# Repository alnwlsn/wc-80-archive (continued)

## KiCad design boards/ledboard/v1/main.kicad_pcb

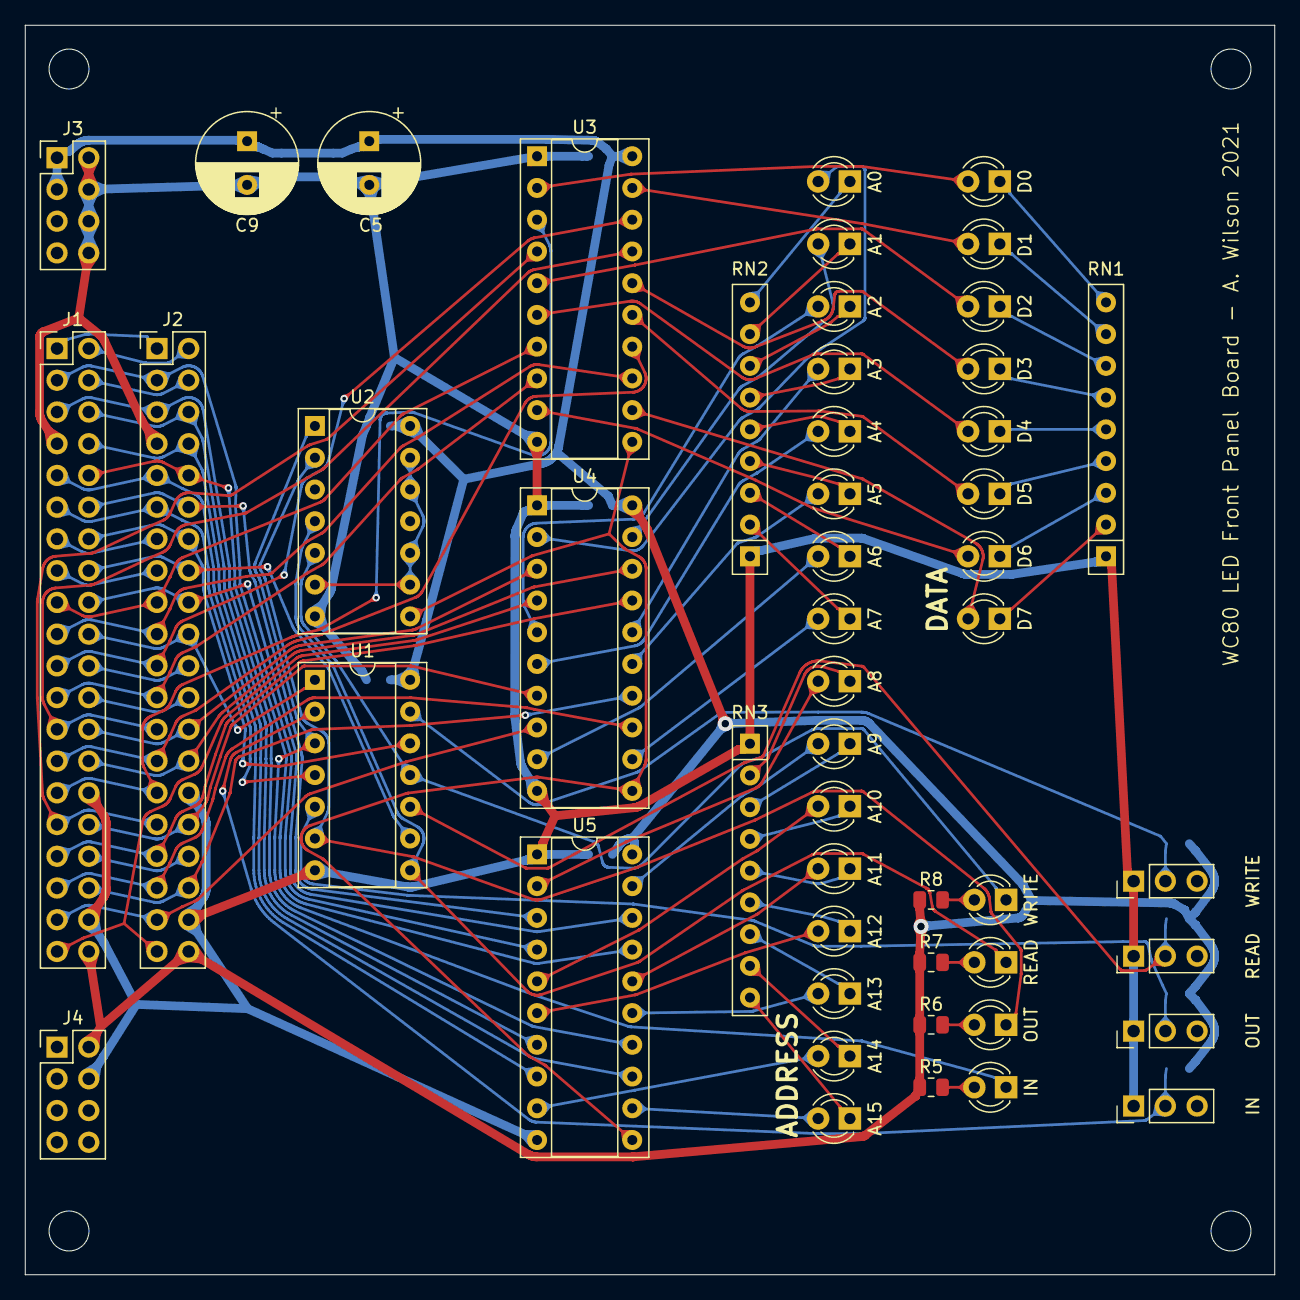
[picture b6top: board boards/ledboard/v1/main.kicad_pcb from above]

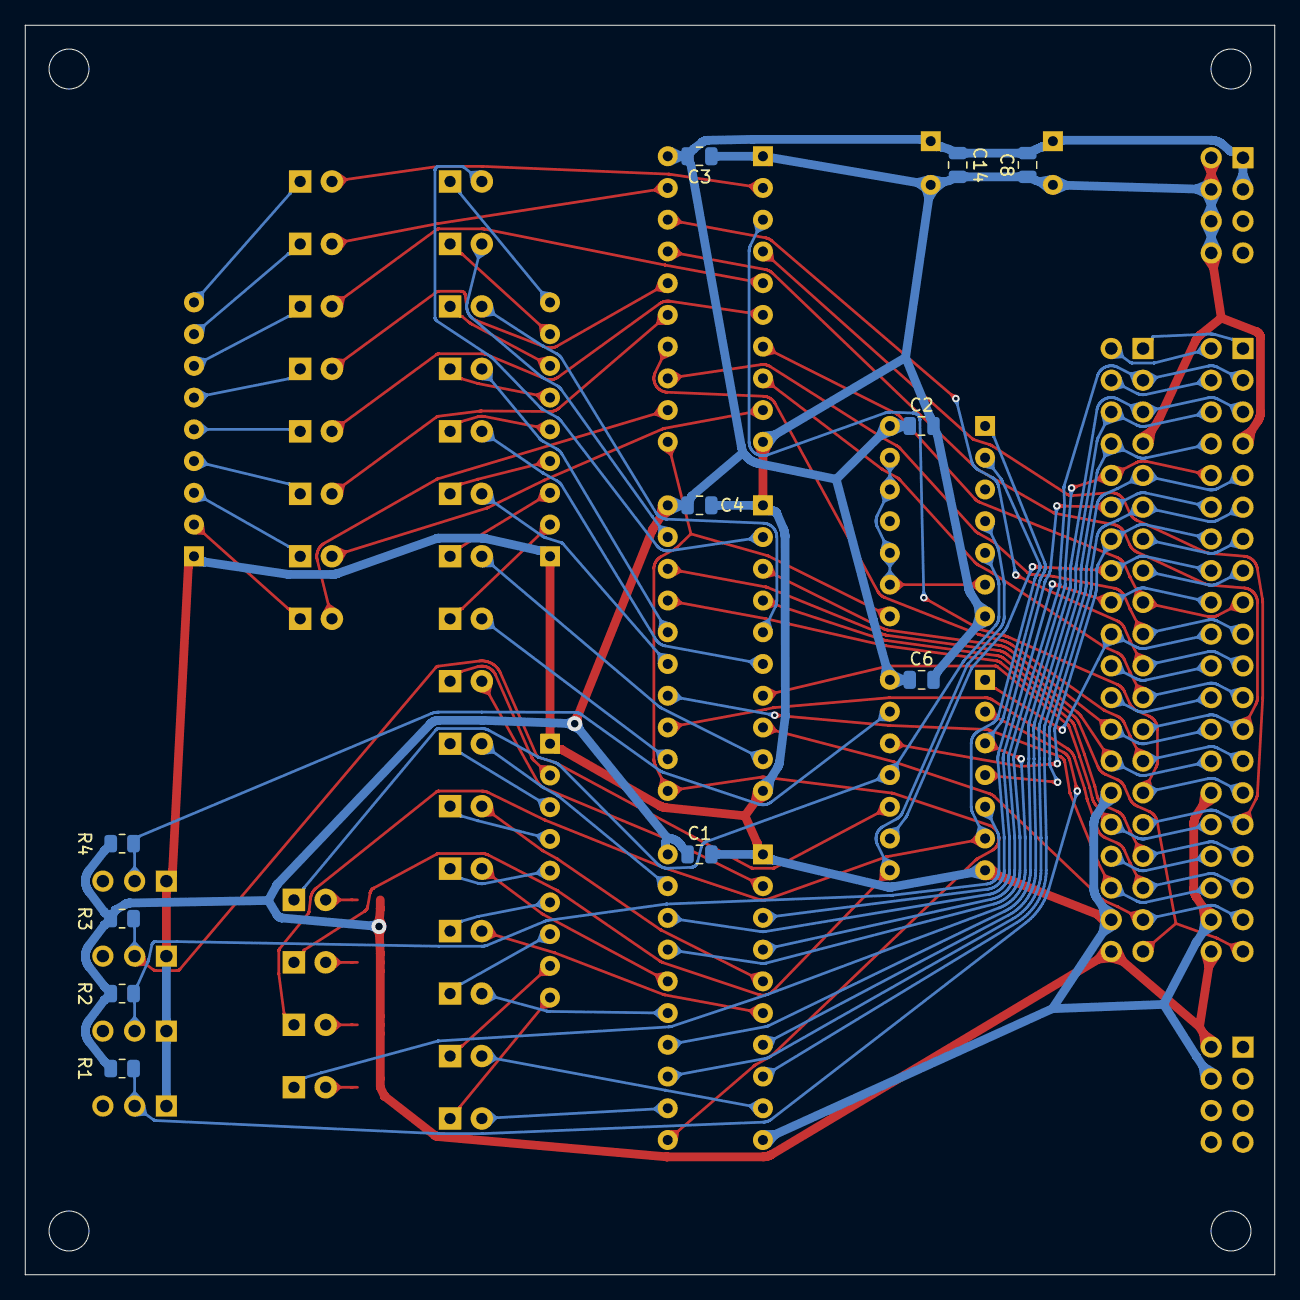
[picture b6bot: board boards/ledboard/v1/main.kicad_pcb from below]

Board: 2 copper layers, 100.0 x 100.0 mm, 65 parts (11 on the bottom side), 100 nets.

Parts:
C1, C2, C3, C4, C6, C8, C14: 100n; C_0805_2012Metric
C5, C9: 470uF; CP_Radial_D8.0mm_P3.50mm
D1: D0; LED_D3.0mm_FlatTop
D2: D2; LED_D3.0mm_FlatTop
D3: D4; LED_D3.0mm_FlatTop
D4: D6; LED_D3.0mm_FlatTop
D5: D7; LED_D3.0mm_FlatTop
D6: D5; LED_D3.0mm_FlatTop
D7: D3; LED_D3.0mm_FlatTop
D8: D1; LED_D3.0mm_FlatTop
D9: A0; LED_D3.0mm_FlatTop
D10: A2; LED_D3.0mm_FlatTop
D11: A4; LED_D3.0mm_FlatTop
D12: A6; LED_D3.0mm_FlatTop
D13: A7; LED_D3.0mm_FlatTop
D14: A5; LED_D3.0mm_FlatTop
D15: A3; LED_D3.0mm_FlatTop
D16: A1; LED_D3.0mm_FlatTop
D17: A8; LED_D3.0mm_FlatTop
D18: A10; LED_D3.0mm_FlatTop
D19: A12; LED_D3.0mm_FlatTop
D20: A14; LED_D3.0mm_FlatTop
D21: A15; LED_D3.0mm_FlatTop
D22: A13; LED_D3.0mm_FlatTop
D23: A11; LED_D3.0mm_FlatTop
D24: A9; LED_D3.0mm_FlatTop
D25: IN; LED_D3.0mm_FlatTop
D26: OUT; LED_D3.0mm_FlatTop
D27: READ; LED_D3.0mm_FlatTop
D28: WRITE; LED_D3.0mm_FlatTop
H1, H2, H3, H4: MountingHole; MountingHole_3.2mm_M3_DIN965
J1, J2: TRS80W-header; PinHeader_2x20_P2.54mm_Vertical
J3, J4: Conn_02x04_Odd_Even; PinHeader_2x04_P2.54mm_Vertical
R1, R2, R3, R4: 4.7K; R_0805_2012Metric
R5, R6, R7, R8: 470; R_0805_2012Metric
RN1, RN2, RN3: 470; R_Array_SIP9
SW1: IN; PinHeader_1x03_P2.54mm_Vertical
SW2: OUT; PinHeader_1x03_P2.54mm_Vertical
SW3: READ; PinHeader_1x03_P2.54mm_Vertical
SW4: WRITE; PinHeader_1x03_P2.54mm_Vertical
U1: 74LS32; DIP-14_W7.62mm_Socket
U2: 74LS20; DIP-14_W7.62mm_Socket
U3, U4, U5: 74LS374; DIP-20_W7.62mm_Socket

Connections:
+5V: C1.1, C2.1, C3.1, C4.1, C5.1, C6.1, C8.1, C9.1, C14.1, J1.40, J2.40, J3.1, J3.3, J4.2, R1.1, R2.1, R3.1, R4.1, R5.1, R6.1, R7.1, R8.1, U1.14, U2.14, U3.20, U4.20, U5.20
CLK: J1.24, J2.24
F_A0: J1.26, J2.26, U4.3
F_A1: J1.28, J2.28, U4.18
F_A2: J1.39, J2.39, U4.4
F_A3: J1.33, J2.33, U4.17
F_A4: J1.32, J2.32, U4.7
F_A5: J1.36, J2.36, U4.14
F_A6: J1.37, J2.37, U4.8
F_A7: J1.35, J2.35, U4.13
F_A8: J1.12, J2.12, U5.3
F_A9: J1.18, J2.18, U5.18
F_A10: J1.3, J2.3, U5.4
F_A11: J1.10, J2.10, U5.17
F_A12: J1.6, J2.6, U5.7
F_A13: J1.5, J2.5, U5.14
F_A14: J1.9, J2.9, U5.8
F_A15: J1.8, J2.8, U5.13
F_D0: J1.29, J2.29, U3.3
F_D1: J1.21, J2.21, U3.18
F_D2: J1.31, J2.31, U3.4
F_D3: J1.25, J2.25, U3.17
F_D4: J1.17, J2.17, U3.7
F_D5: J1.27, J2.27, U3.14
F_D6: J1.23, J2.23, U3.8
F_D7: J1.19, J2.19, U3.13
GND: C1.2, C2.2, C3.2, C4.2, C5.2, C6.2, C8.2, C9.2, C14.2, J1.7, J1.30, J1.38, J2.7, J2.30, J2.38, J3.2, J3.4, J3.6, J3.8, J4.4, RN1.1, RN2.1, RN3.1, SW1.1, SW2.1, SW3.1, SW4.1, U1.7, U2.7, U3.1, U3.10, U4.1, U4.10, U5.1, U5.10
unnamed: D1.1, RN1.9
unnamed: D1.2, U3.2
unnamed: D2.1, RN1.7
unnamed: D2.2, U3.5
unnamed: D3.1, RN1.5
unnamed: D3.2, U3.6
unnamed: D4.1, RN1.3
unnamed: D4.2, U3.9
unnamed: D5.1, RN1.2
unnamed: D5.2, U3.12
unnamed: D6.1, RN1.4
unnamed: D6.2, U3.15
unnamed: D7.1, RN1.6
unnamed: D7.2, U3.16
unnamed: D8.1, RN1.8
unnamed: D8.2, U3.19
unnamed: D9.1, RN2.9
unnamed: D9.2, U4.2
unnamed: D10.1, RN2.7
unnamed: D10.2, U4.5
unnamed: D11.1, RN2.5
unnamed: D11.2, U4.6
unnamed: D12.1, RN2.3
unnamed: D12.2, U4.9
unnamed: D13.1, RN2.2
unnamed: D13.2, U4.12
unnamed: D14.1, RN2.4
unnamed: D14.2, U4.15
unnamed: D15.1, RN2.6
unnamed: D15.2, U4.16
unnamed: D16.1, RN2.8
unnamed: D16.2, U4.19
unnamed: D17.1, RN3.2
unnamed: D17.2, U5.2
unnamed: D18.1, RN3.4
unnamed: D18.2, U5.5
unnamed: D19.1, RN3.6
unnamed: D19.2, U5.6
unnamed: D20.1, RN3.8
unnamed: D20.2, U5.9
unnamed: D21.1, RN3.9
unnamed: D21.2, U5.12
unnamed: D22.1, RN3.7
unnamed: D22.2, U5.15
unnamed: D23.1, RN3.5
unnamed: D23.2, U5.16
unnamed: D24.1, RN3.3
unnamed: D24.2, U5.19
unnamed: D25.1, U1.3, U2.1
unnamed: D25.2, R5.2
unnamed: D26.1, U1.6, U2.2
unnamed: D26.2, R6.2
unnamed: D27.1, U1.8, U2.4
unnamed: D27.2, R7.2
unnamed: D28.1, U1.11, U2.5
unnamed: D28.2, R8.2
unnamed: R1.2, SW1.2, U1.2
unnamed: R2.2, SW2.2, U1.5
unnamed: R3.2, SW3.2, U1.10
unnamed: R4.2, SW4.2, U1.13
unnamed: U2.8, U3.11, U4.11, U5.11
unnamed: U2.6, U2.9, U2.10, U2.12, U2.13
~F_EXMEM~: J1.4, J2.4
~F_INTAK~: J1.13, J2.13
~F_INT~: J1.22, J2.22
~F_INUSE~: J1.15, J2.15
~F_IN~: J1.20, J2.20, U1.1
~F_MREQ~: J1.2, J2.2
~F_OUT~: J1.11, J2.11, U1.4
~F_READ~: J1.16, J2.16, U1.9
~F_SYSRES~: J1.1, J2.1
~F_WAIT~: J1.34, J2.34
~F_WRITE~: J1.14, J2.14, U1.12

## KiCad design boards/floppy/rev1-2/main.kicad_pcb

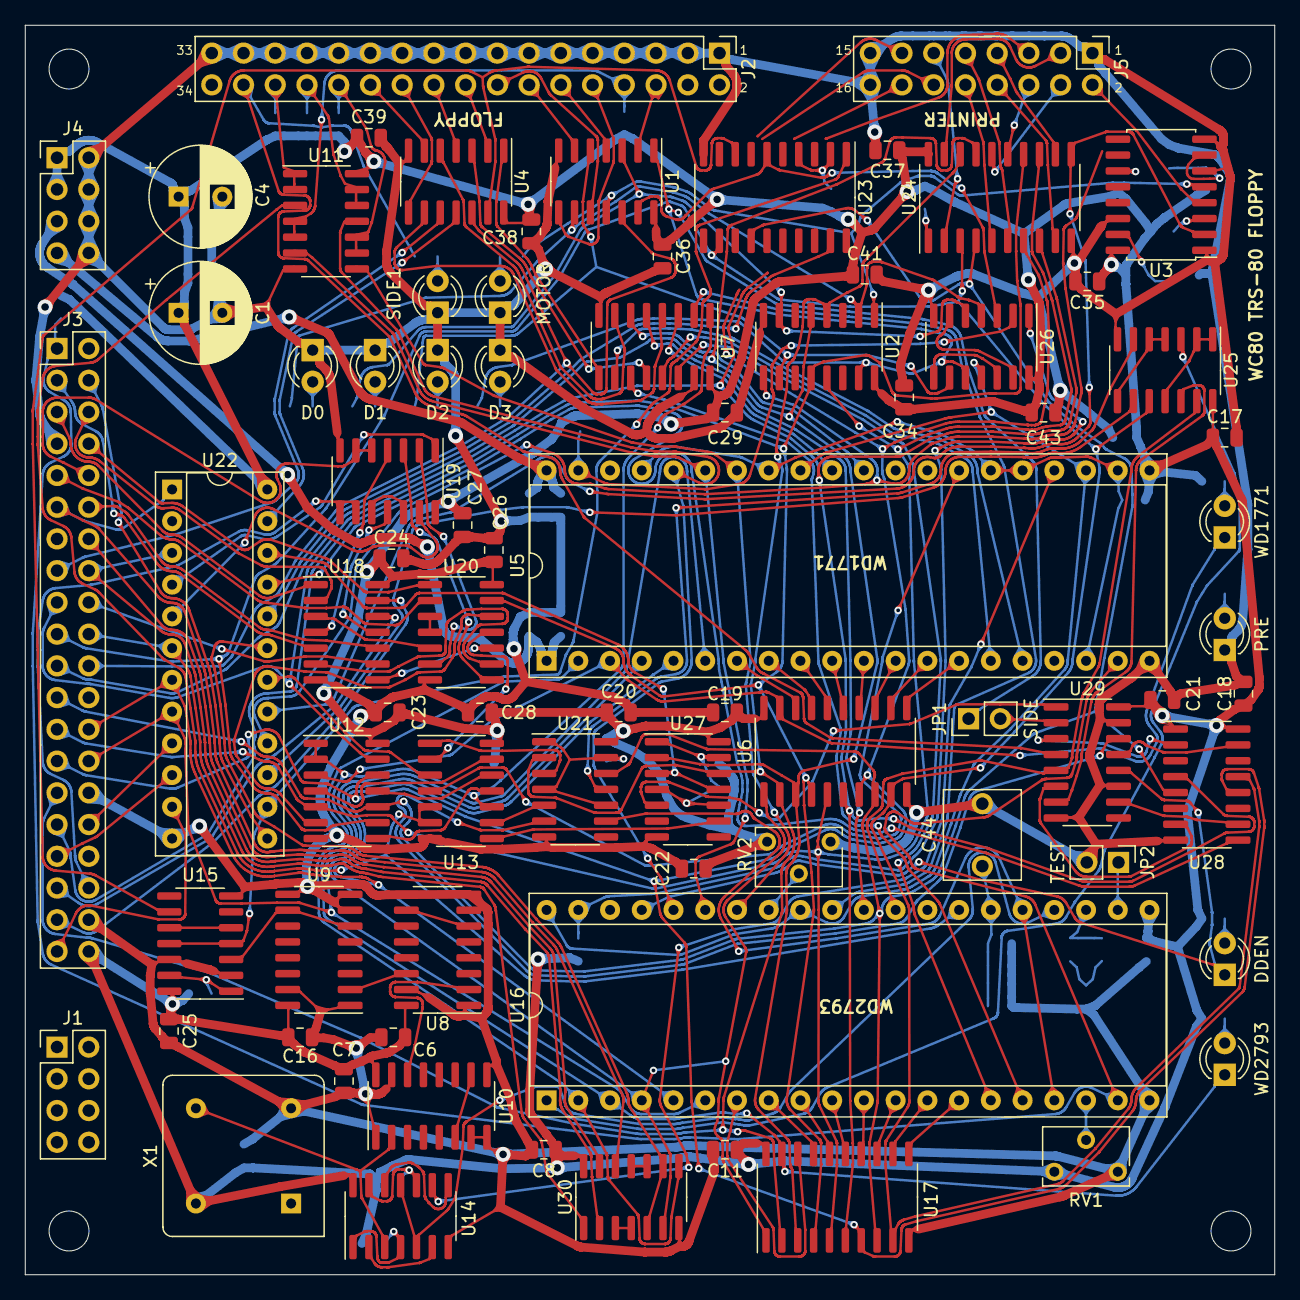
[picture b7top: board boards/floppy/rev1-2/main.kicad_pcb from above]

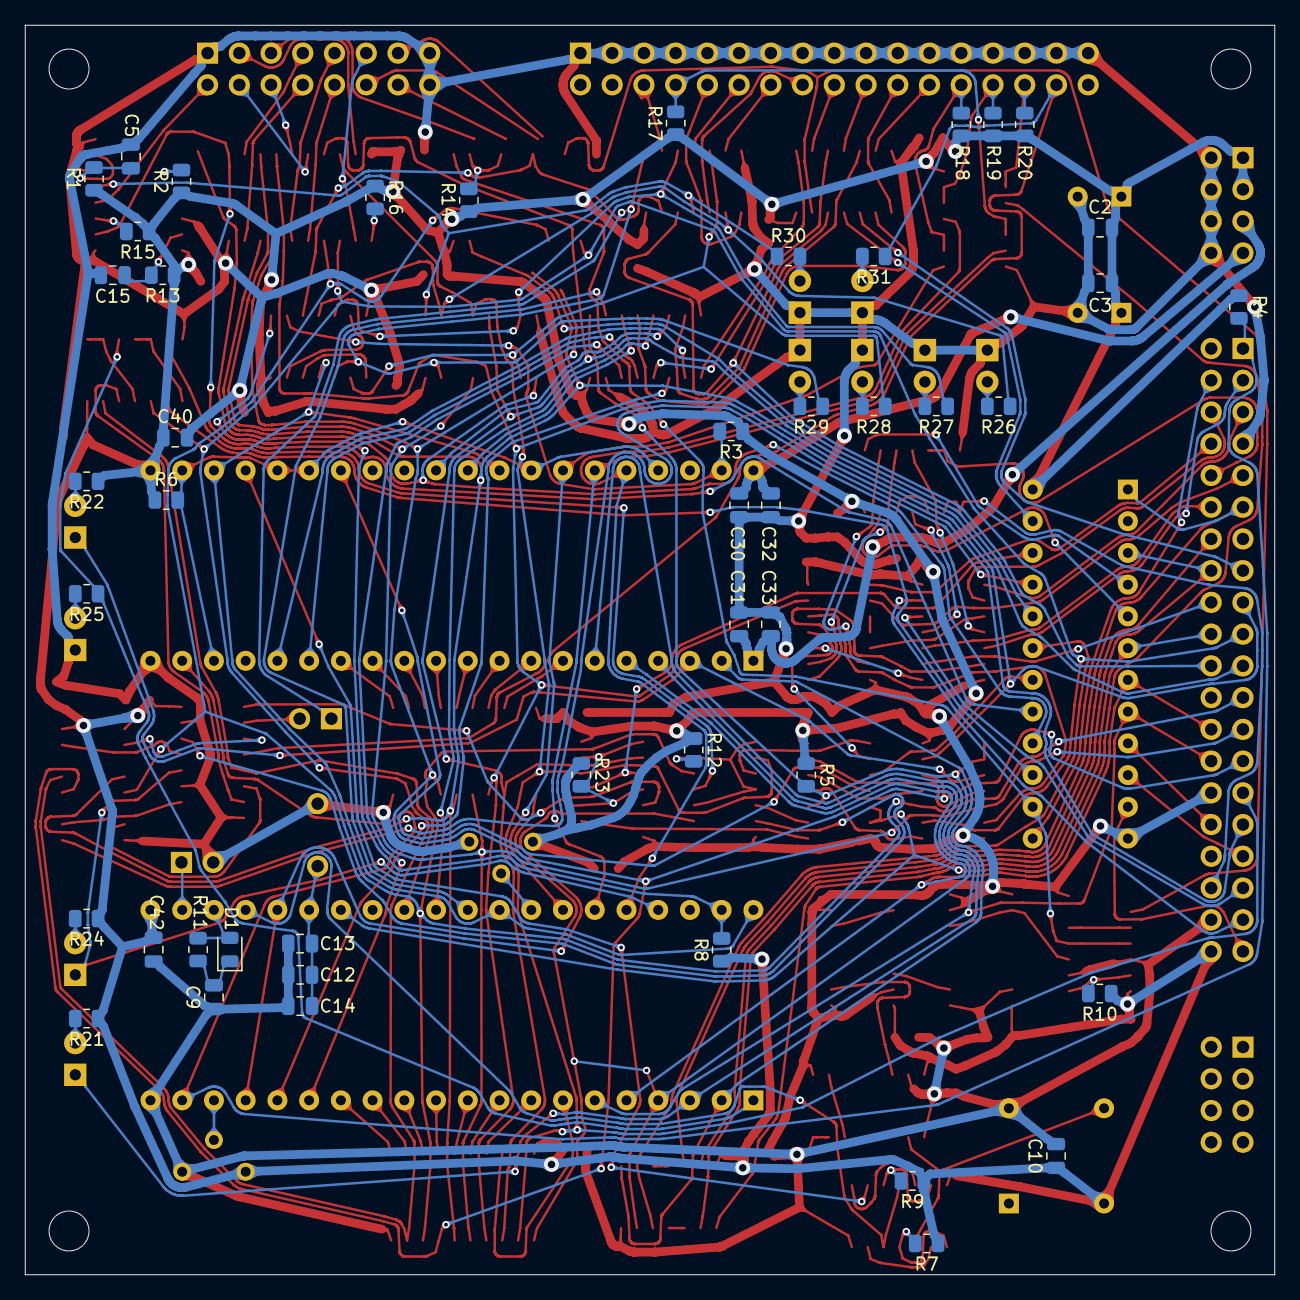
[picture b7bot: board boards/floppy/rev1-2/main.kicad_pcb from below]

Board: 2 copper layers, 100.0 x 100.0 mm, 130 parts (47 on the bottom side), 198 nets.

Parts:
C1, C4: 470uF; CP_Radial_D8.0mm_P3.50mm
C2, C3, C6, C7, C8, C10, C11, C16, C17, C18, C19, C20, C21, C22, C23, C24, C25, C26, C27, C28, C29, C30, C31, C32, C33, C34, C35, C36, C37, C38, C39, C40, C41, C42, C43: 100n; C_0805_2012Metric
C5: 33uF; C_0805_2012Metric
C9: 150nF; C_0805_2012Metric
C12, C13, C14: 15pF; C_0805_2012Metric
C15: 200p; C_0805_2012Metric
C44: 60pF; C_Rect_L7.0mm_W6.0mm_P5.00mm
D1: DIODE; D_0805_2012Metric
D2: WD2793; LED_D3.0mm
D3: WD1771; LED_D3.0mm
D4: DDEN; LED_D3.0mm
D5: PRE; LED_D3.0mm
D6: D0; LED_D3.0mm
D7: D1; LED_D3.0mm
D8: D2; LED_D3.0mm
D9: D3; LED_D3.0mm
D10: MOTOR; LED_D3.0mm
D11: SIDE1; LED_D3.0mm
J1, J4: Conn_02x04_Odd_Even; PinHeader_2x04_P2.54mm_Vertical
J2: Floppy-header; PinHeader_2x17_P2.54mm_Vertical
J3: TRS80W-header; PinHeader_2x20_P2.54mm_Vertical
J5: Conn_01x16_Male; PinHeader_2x08_P2.54mm_Vertical
JP1: SIDE; PinHeader_1x02_P2.54mm_Vertical
JP2: TEST; PinHeader_1x02_P2.54mm_Vertical
M1, M2, M3, M4: 3mm-mounting-hole; MountingHole_3.2mm_M3_DIN965
R1: 200K; R_0805_2012Metric
R2, R15, R16: 4K7; R_0805_2012Metric
R3, R4, R5, R6, R7, R8, R9, R10, R12, R14, R23: 10K; R_0805_2012Metric
R11: 1K; R_0805_2012Metric
R13: 20K; R_0805_2012Metric
R17, R18, R19, R20: 150; R_0805_2012Metric
R21, R22, R24, R25, R26, R27, R28, R29, R30, R31: 470; R_0805_2012Metric
RV1: 50K; Potentiometer_Bourns_3266W_Vertical
RV2: 10K; Potentiometer_Bourns_3266W_Vertical
U1, U4: 74LS06; SOIC-14_3.9x8.7mm_P1.27mm
U2, U28: 74LS175; SOP-16_3.9x9.9mm_P1.27mm
U3: 74LS123; SO-16_5.3x10.2mm_P1.27mm
U5: WD1771; DIP-40_W15.24mm_Socket
U6: 74LS640; SO-20_5.3x12.6mm_P1.27mm
U7, U29: 74LS157; SOP-16_3.9x9.9mm_P1.27mm
U8, U9, U10: 4518; SOP-16_3.9x9.9mm_P1.27mm
U11: 74LS08; SOIC-14_3.9x8.7mm_P1.27mm
U12, U18, U25, U30: 74LS00; SOIC-14_3.9x8.7mm_P1.27mm
U13, U19: 74LS02; SOIC-14_3.9x8.7mm_P1.27mm
U14, U15, U21, U27: 74LS74; SOIC-14_3.9x8.7mm_P1.27mm
U16: WD2793; DIP-40_W15.24mm_Socket
U17: 74LS245; SO-20_5.3x12.6mm_P1.27mm
U20, U26: 74LS32; SOIC-14_3.9x8.7mm_P1.27mm
U22: ATF22V10C; DIP-24_W7.62mm_Socket
U23: 74LS244; SO-20_5.3x12.6mm_P1.27mm
U24: 74LS273; SO-20_5.3x12.6mm_P1.27mm
X1: CXO_DIP8; Oscillator_DIP-8

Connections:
1MHz: U5.24, U14.9
2MHz: U14.5, U14.11, U16.24
4MHz: U10.2, U14.3, X1.5
37XX: U19.1, U22.4
40Hz: U9.6, U9.10, U15.3
58SEL: U22.15, U25.9
+5V: C1.1, C2.1, C3.1, C4.1, C6.1, C7.1, C8.1, C10.1, C11.1, C16.1, C17.1, C18.1, C19.1, C20.1, C21.1, C22.1, C23.1, C24.1, C25.1, C26.1, C27.1, C28.1, C29.1, C34.1, C35.1, C36.1, C37.1, C38.1, C39.1, C40.1, C41.1, C42.1, C43.1, J3.40, J4.1, J4.3, R1.1, R2.1, R3.1, R4.1, R5.1, R6.1, R7.1, R8.1, R9.1, R10.1, R12.1, R13.1, R14.1, R15.1, R16.1, R17.1, R18.1, R19.1, R20.1, R21.1, R22.1, R23.1, R24.1, RV1.1, RV2.3, U1.14, U2.16, U3.16, U4.14, U5.21, U6.20, U7.16, U8.16, U9.16, U10.16, U11.14, U12.14, U13.14, U14.14, U15.14, U16.21, U17.20, U18.14, U19.14, U20.14, U21.14, U22.24, U23.20, U24.20, U25.14, U26.14, U27.14, U28.1, U29.16, U30.14, X1.8
+12V: C30.1, C32.1, J4.7, U5.40
-5V: C31.1, C33.1, J4.5, U5.1
CENP: R25.1, U16.1, U25.3
D0: R26.1, U1.9, U2.2, U26.4
D1: R27.1, U1.3, U2.7, U26.5
D2: R28.1, U1.5, U2.10, U26.9
D3: JP1.1, R29.1, U1.1, U2.15, U26.10
DFH: U22.21, U28.9
DFL: U2.9, U3.9, U22.16
EFX: U19.13, U22.5
FLOP: U22.19, U30.5, U30.9
FSIDE: J2.32, R31.1, U29.4
F_A0: J3.26, U5.5, U16.5, U22.7
F_A1: J3.28, U5.6, U16.6, U22.8
F_A2: J3.39, U22.11
F_A3: J3.33, U22.10
F_A4: J3.32, U22.9
F_A5: J3.36, U19.8, U19.9
F_A6: J3.37, U18.13
F_A7: J3.35, U18.12
F_A8: J3.12, U18.10
F_A9: J3.18, U18.9
F_A10: J3.3, U18.5
F_A11: J3.10, U19.5, U19.6
F_A12: J3.6, U18.2
F_A13: J3.5, U18.1
F_A14: J3.9, U20.2
F_A15: J3.8, U20.1
F_D0: J3.29, U2.4, U6.2, U17.2, U21.2, U24.18, U27.12
F_D1: J3.21, U2.5, U6.3, U17.3, U24.17, U27.2
F_D2: J3.31, U2.12, U6.4, U17.4, U20.13, U24.14
F_D3: J3.25, U2.13, U6.5, U12.5, U17.5, U24.13
F_D4: J3.17, U6.6, U12.13, U17.6, U23.3, U24.8, U28.4
F_D5: J3.27, U6.7, U12.12, U17.7, U23.5, U24.7, U28.12
F_D6: J3.23, U6.8, U12.10, U17.8, U21.12, U23.7, U23.14, U24.4, U28.5
F_D7: J3.19, U6.9, U12.9, U17.9, U23.9, U23.12, U24.3, U25.10, U28.13
GND: C1.2, C2.2, C3.2, C4.2, C5.2, C6.2, C7.2, C8.2, C9.1, C10.2, C11.2, C12.1, C13.1, C14.1, C15.2, C16.2, C17.2, C18.2, C19.2, C20.2, C21.2, C22.2, C23.2, C24.2, C25.2, C26.2, C27.2, C28.2, C29.2, C30.2, C31.2, C32.2, C33.2, C34.2, C35.2, C36.2, C37.2, C38.2, C39.2, C40.2, C41.2, C42.2, C43.2, C44.2, D5.1, D6.1, D7.1, D8.1, D9.1, D10.1, D11.1, J2.1, J2.3, J2.5, J2.7, J2.9, J2.11, J2.13, J2.15, J2.17, J2.19, J2.21, J2.23, J2.25, J2.27, J2.29, J2.31, J2.33, J3.7, J3.30, J3.38, J4.2, J4.4, J4.6, J4.8, J5.1, J5.15, J5.16, JP2.2, RV1.3, RV2.1, U1.7, U2.8, U3.1, U3.6, U3.8, U3.14, U4.7, U5.20, U6.10, U7.8, U7.15, U8.1, U8.7, U8.8, U8.9, U8.15, U9.1, U9.7, U9.8, U9.9, U9.15, U10.1, U10.7, U10.8, U10.9, U10.15, U11.7, U12.7, U13.7, U14.7, U15.2, U15.7, U15.12, U16.20, U17.10, U18.7, U19.7, U20.7, U21.7, U22.12, U23.10, U24.10, U25.7, U26.7, U27.7, U28.8, U29.8, U29.11, U29.15, U30.7, X1.4
INTCLK: U4.13, U15.9, U23.8
INTFLOP: U1.13, U23.6
M1PRE: U16.29, U25.13, U29.5
M1SIDE: JP1.2, U29.2
MOTOR: R30.1, U1.11, U2.1, U3.5
unnamed: C5.1, R1.2, U3.7
unnamed: C9.2, D1.1, R11.1
unnamed: C12.2, C13.2, C14.2, C44.1, U16.26
unnamed: C15.1, R13.2, U3.15
unnamed: D1.2, R11.2, U16.23
unnamed: D2.2, R21.2
unnamed: D3.2, R22.2
unnamed: D4.2, R24.2
unnamed: D5.2, R25.2
unnamed: D6.2, R26.2
unnamed: D7.2, R27.2
unnamed: D8.2, R28.2
unnamed: D9.2, R29.2
unnamed: D10.2, R30.2
unnamed: D11.2, R31.2
unnamed: J2.6, U1.2
unnamed: J2.8, R17.2
unnamed: J2.10, U1.8
unnamed: J2.12, U1.4
unnamed: J2.14, U1.6
unnamed: J2.16, U1.10
unnamed: J2.18, U4.2
unnamed: J2.20, U4.4
unnamed: J2.22, U4.8
unnamed: J2.24, U4.6
unnamed: J2.26, R18.2
unnamed: J2.28, R19.2
unnamed: J2.30, R20.2, U26.1, U26.2
unnamed: J5.2, U3.4
unnamed: J5.3, U24.19
unnamed: J5.4, U24.16
unnamed: J5.5, U23.17
unnamed: J5.6, U24.15
unnamed: J5.7, U24.12
unnamed: J5.8, U24.9
unnamed: J5.9, U24.6
unnamed: J5.10, U24.5
unnamed: J5.11, U24.2
unnamed: J5.12, U23.11
unnamed: J5.13, U23.13
unnamed: J5.14, U23.15
unnamed: JP2.1, U16.22
unnamed: R2.2, U3.10, U3.11
unnamed: R3.2, U5.39
unnamed: R6.2, U5.18, U5.22, U5.25, U5.26, U5.33, U5.37
unnamed: R7.2, U14.1, U14.4
unnamed: R8.2, U16.39
unnamed: R9.2, U14.10, U14.13
unnamed: R10.2, U15.1, U15.13
unnamed: R12.2, U21.1, U21.4, U21.10, U21.13
unnamed: R14.2, U23.2, U23.4
unnamed: R15.2, U3.3
unnamed: R16.2, U24.1
unnamed: R23.2, U27.1, U27.4, U27.10, U27.13
unnamed: RV1.2, U16.18
unnamed: RV2.2, U16.33
unnamed: U4.1, U7.9
unnamed: U4.3, U7.12
unnamed: U4.5, U7.7
unnamed: U4.9, U7.4
unnamed: U5.7, U6.18
unnamed: U5.8, U6.17
unnamed: U5.9, U6.16
unnamed: U5.10, U6.15
unnamed: U5.11, U6.14
unnamed: U5.12, U6.13
unnamed: U5.13, U6.12
unnamed: U5.14, U6.11
unnamed: U5.15, U7.13
unnamed: U5.16, U7.10
unnamed: U5.30, U7.6
unnamed: U5.31, U7.3
unnamed: U8.6, U8.10
unnamed: U8.14, U9.2
unnamed: U10.6, U10.10
unnamed: U8.2, U10.14
unnamed: U12.4, U13.13
unnamed: U12.6, U20.12
unnamed: U12.8, U13.11
unnamed: U12.11, U13.12
unnamed: U13.1, U21.3
unnamed: U13.2, U20.11
unnamed: U5.27, U13.4
unnamed: U13.5, U13.6, U16.27, U26.3
unnamed: U13.8, U27.9
unnamed: U13.9, U21.5
unnamed: U14.2, U14.6
unnamed: U14.8, U14.12
unnamed: U15.5, U15.10
unnamed: U5.2, U16.2, U30.8
unnamed: U5.4, U6.1, U16.4, U17.1, U30.6
unnamed: U16.7, U17.18
unnamed: U16.8, U17.17
unnamed: U16.9, U17.16
unnamed: U16.10, U17.15
unnamed: U16.11, U17.14
unnamed: U16.12, U17.13
unnamed: U16.13, U17.12
unnamed: U16.14, U17.11
unnamed: U7.14, U16.15
unnamed: U7.11, U16.16
unnamed: U16.17, U16.25, U21.9
unnamed: U7.5, U16.30
unnamed: U7.2, U16.31
unnamed: U5.23, U5.32, U16.32, U16.40, U26.11
unnamed: U5.34, U16.34
unnamed: U5.35, U16.35
unnamed: U5.36, U16.36
unnamed: U18.3, U20.5
unnamed: U18.4, U19.4
unnamed: U18.6, U20.9
unnamed: U18.8, U20.10
unnamed: U18.11, U19.11
unnamed: U19.2, U20.6
unnamed: U19.3, U20.8
unnamed: U19.10, U19.12
unnamed: U20.3, U20.4
unnamed: U21.11, U25.6
unnamed: U4.11, U22.23
unnamed: U25.1, U25.2, U25.11
unnamed: U25.4, U25.5, U25.8
unnamed: U25.12, U29.7
unnamed: U26.8, U26.12
unnamed: U26.6, U26.13
unnamed: U27.5, U29.1
unnamed: U28.2, U29.3
unnamed: U28.7, U29.6
unnamed: U28.10, U29.10
unnamed: U28.15, U29.13
unnamed: U30.3, U30.4
unnamed: U30.10, U30.11
OPT: U22.22, U27.3, U27.11
~37E0~: U15.4, U15.11, U22.14, U23.1
~1771~: D3.1, U5.3, U6.19, U12.3
~2793~: D2.1, R5.2, U7.1, U12.1, U12.2, U13.10, U16.3, U17.19
~CDDEN~: D4.1, U16.37, U29.12
~DENSEL~: U13.3, U22.18
~F_EXMEM~: J3.4, U22.13
~F_INT~: J3.22, U1.12, U4.12
~F_INUSE~: J3.15, U4.10
~F_IN~: J3.20, U22.6, U30.1
~F_MEMRQ~: J3.2, U22.2
~F_OUT~: J3.11, U22.1, U30.12
~F_READ~: J3.16, U22.3, U30.2
~F_SYSRES~: J3.1, R4.2, U5.19, U16.19
~F_WRITE~: J3.14, U30.13
~MDDEN~: U21.6, U29.14
~PRINTREAD~: U22.20, U23.19
~PRINTWRITE~: U3.2, U22.17, U24.11

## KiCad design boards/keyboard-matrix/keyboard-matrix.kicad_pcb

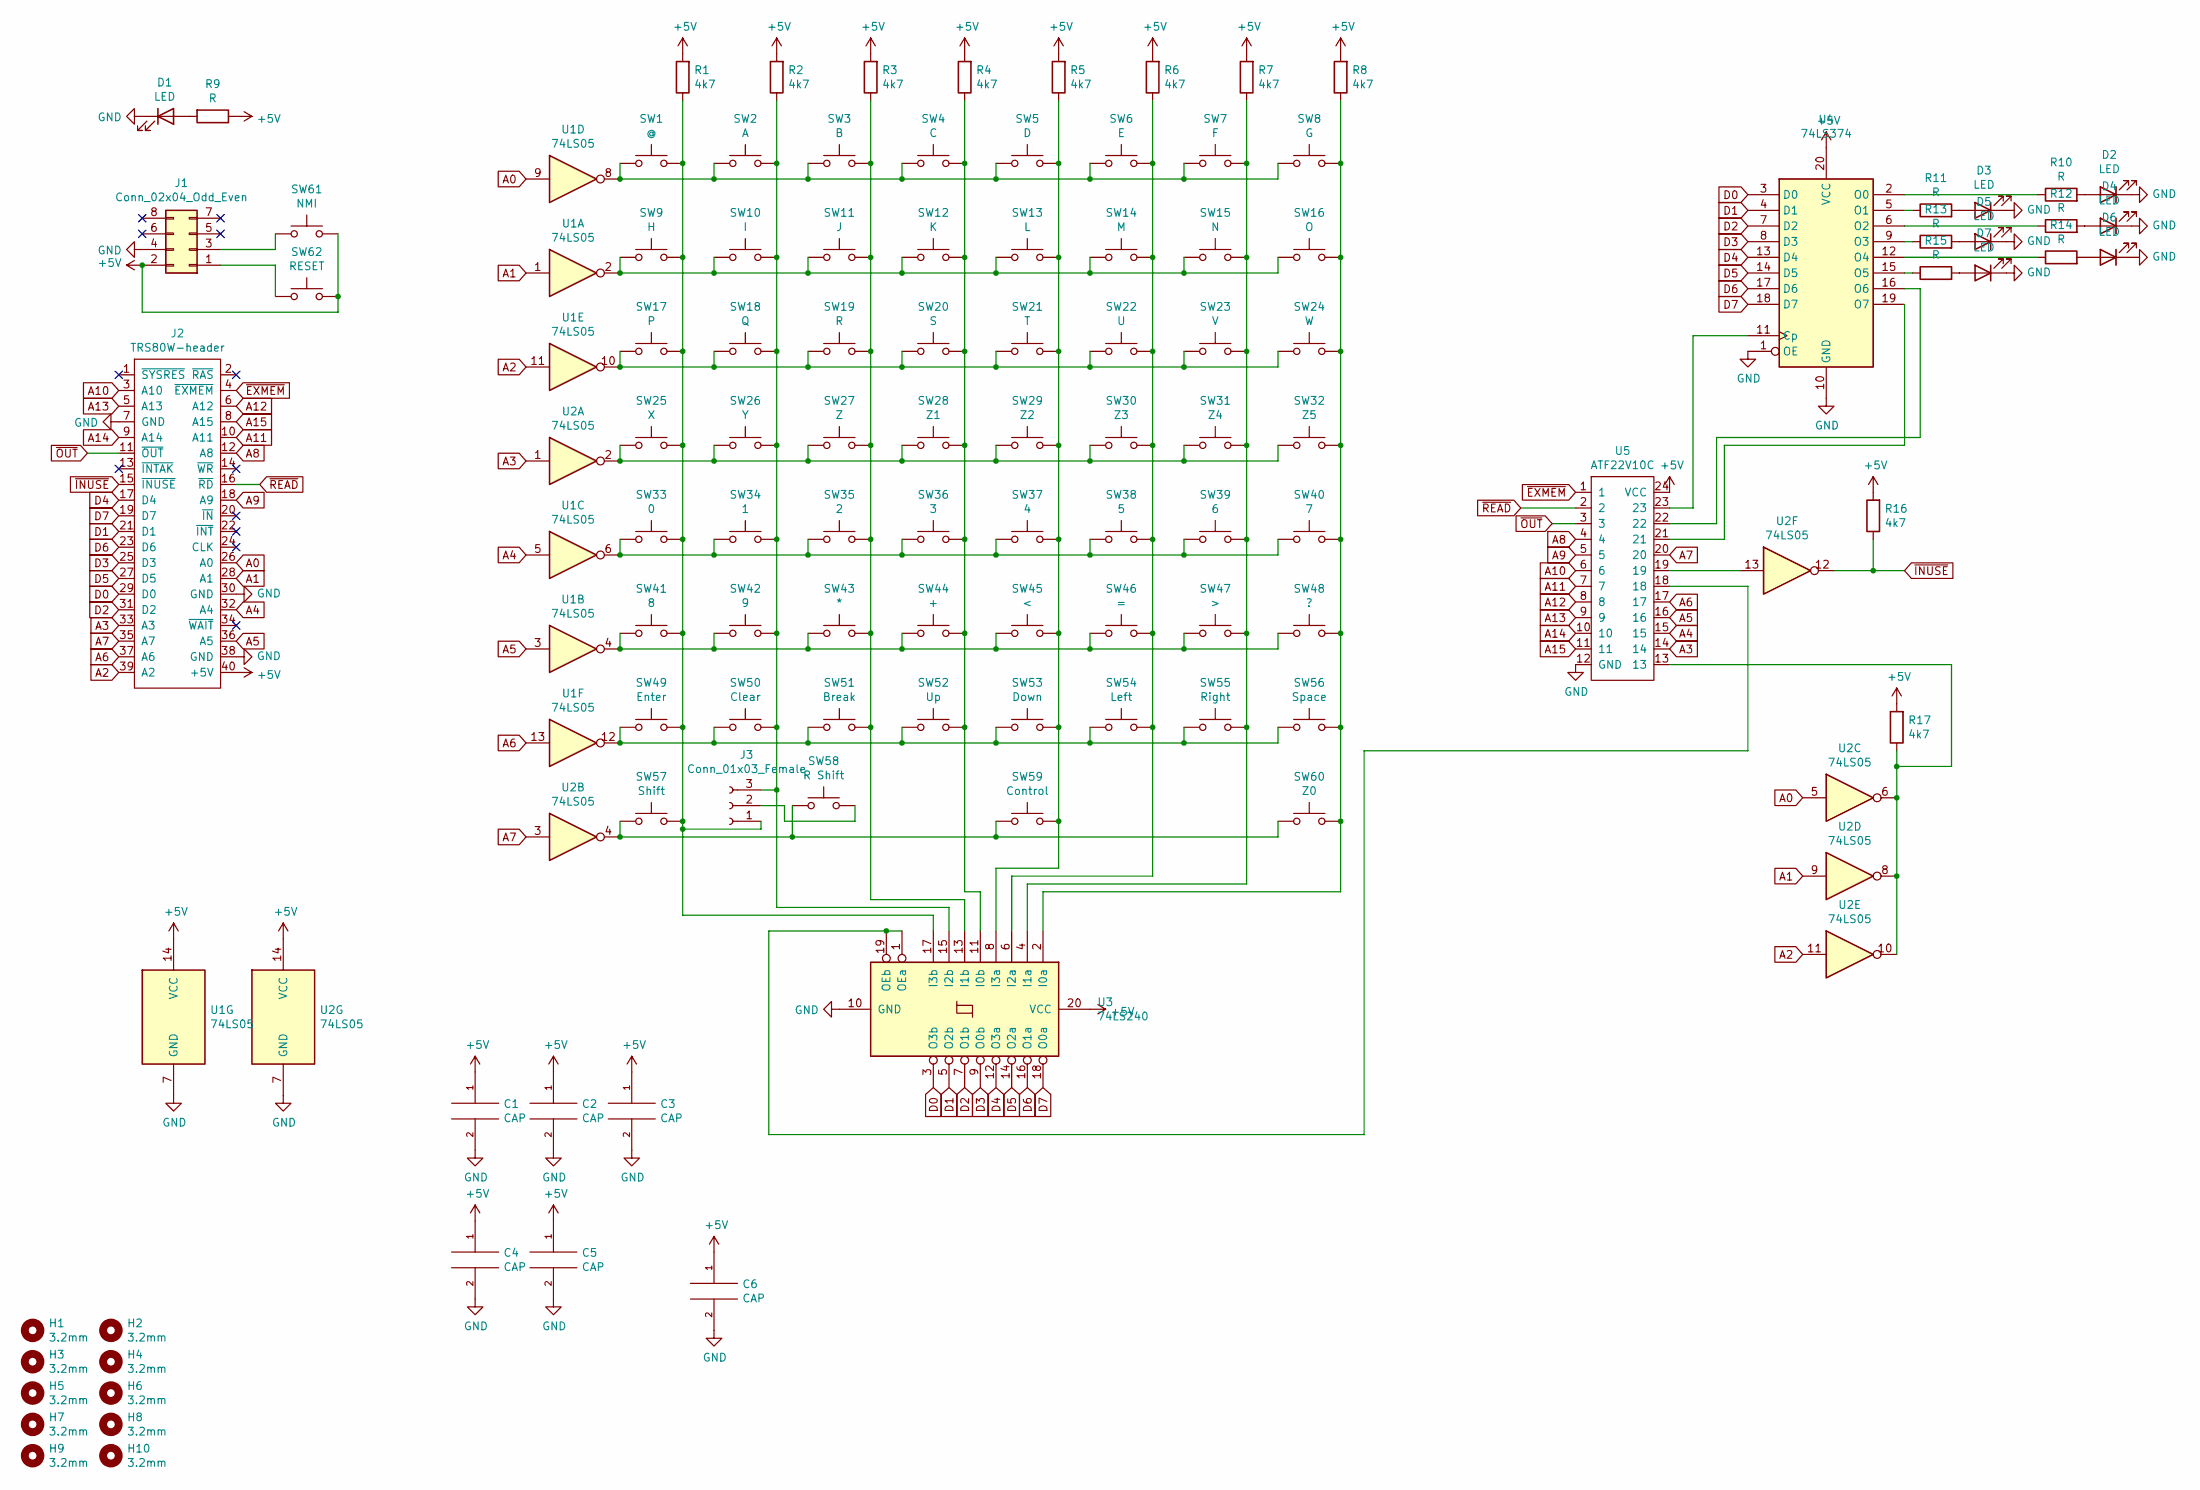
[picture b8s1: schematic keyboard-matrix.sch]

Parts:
C1, C2, C3, C4, C5: CAP; C_0805_2012Metric
C6: CAP; CP_Radial_D8.0mm_P3.50mm
D1, D2, D3, D4, D5, D6, D7: LED; LED_D3.0mm
H1, H2, H3, H4, H5, H6, H7, H8, H9, H10: 3.2mm; MountingHole_3.2mm_M3_DIN965
J1: Conn_02x04_Odd_Even; PinHeader_2x04_P2.54mm_Vertical
J2: TRS80W-header; PinHeader_2x20_P2.54mm_Vertical
J3: Conn_01x03_Female; SolderJumper-3_P1.3mm_Open_Pad1.0x1.5mm
R1, R2, R3, R4, R5, R6, R7, R8, R16, R17: 4k7; R_0805_2012Metric
R9, R10, R11, R12, R13, R14, R15: R; R_0805_2012Metric
SW1: @; SW_Cherry_MX_1.00u_PCB
SW2: A; SW_Cherry_MX_1.00u_PCB
SW3: B; SW_Cherry_MX_1.00u_PCB
SW4: C; SW_Cherry_MX_1.00u_PCB
SW5: D; SW_Cherry_MX_1.00u_PCB
SW6: E; SW_Cherry_MX_1.00u_PCB
SW7: F; SW_Cherry_MX_1.00u_PCB
SW8: G; SW_Cherry_MX_1.00u_PCB
SW9: H; SW_Cherry_MX_1.00u_PCB
SW10: I; SW_Cherry_MX_1.00u_PCB
SW11: J; SW_Cherry_MX_1.00u_PCB
SW12: K; SW_Cherry_MX_1.00u_PCB
SW13: L; SW_Cherry_MX_1.00u_PCB
SW14: M; SW_Cherry_MX_1.00u_PCB
SW15: N; SW_Cherry_MX_1.00u_PCB
SW16: O; SW_Cherry_MX_1.00u_PCB
SW17: P; SW_Cherry_MX_1.00u_PCB
SW18: Q; SW_Cherry_MX_1.00u_PCB
SW19: R; SW_Cherry_MX_1.00u_PCB
SW20: S; SW_Cherry_MX_1.00u_PCB
SW21: T; SW_Cherry_MX_1.00u_PCB
SW22: U; SW_Cherry_MX_1.00u_PCB
SW23: V; SW_Cherry_MX_1.00u_PCB
SW24: W; SW_Cherry_MX_1.00u_PCB
SW25: X; SW_Cherry_MX_1.00u_PCB
SW26: Y; SW_Cherry_MX_1.00u_PCB
SW27: Z; SW_Cherry_MX_1.00u_PCB
SW28: Z1; SW_Cherry_MX_1.00u_PCB
SW29: Z2; SW_Cherry_MX_1.00u_PCB
SW30: Z3; SW_Cherry_MX_1.00u_PCB
SW31: Z4; SW_Cherry_MX_1.00u_PCB
SW32: Z5; SW_Cherry_MX_1.00u_PCB
SW33: 0; SW_Cherry_MX_1.00u_PCB
SW34: 1; SW_Cherry_MX_1.00u_PCB
SW35: 2; SW_Cherry_MX_1.00u_PCB
SW36: 3; SW_Cherry_MX_1.00u_PCB
SW37: 4; SW_Cherry_MX_1.00u_PCB
SW38: 5; SW_Cherry_MX_1.00u_PCB
SW39: 6; SW_Cherry_MX_1.00u_PCB
SW40: 7; SW_Cherry_MX_1.00u_PCB
SW41: 8; SW_Cherry_MX_1.00u_PCB
SW42: 9; SW_Cherry_MX_1.00u_PCB
SW43: *; SW_Cherry_MX_1.00u_PCB
SW44: +; SW_Cherry_MX_1.00u_PCB
SW45: <; SW_Cherry_MX_1.00u_PCB
SW46: =; SW_Cherry_MX_1.00u_PCB
SW47: >; SW_Cherry_MX_1.00u_PCB
SW48: ?; SW_Cherry_MX_1.00u_PCB
SW49: Enter; SW_Cherry_MX_2.00u_PCB
SW50: Clear; SW_Cherry_MX_1.00u_PCB
SW51: Break; SW_Cherry_MX_1.00u_PCB
SW52: Up; SW_Cherry_MX_1.00u_PCB
SW53: Down; SW_Cherry_MX_1.00u_PCB
SW54: Left; SW_Cherry_MX_1.00u_PCB
SW55: Right; SW_Cherry_MX_1.00u_PCB
SW56: Space; SW_Cherry_MX_6.25u_PCB
SW57: Shift; SW_Cherry_MX_1.50u_PCB
SW58: R Shift; SW_Cherry_MX_1.50u_Plate
SW59: Control; SW_Cherry_MX_1.00u_PCB
SW60: Z0; SW_Cherry_MX_1.00u_PCB
SW61: NMI; SW_Cherry_MX_1.00u_PCB
SW62: RESET; SW_Cherry_MX_1.00u_PCB
U1, U2: 74LS05; DIP-14_W7.62mm
U3: 74LS240; DIP-20_W7.62mm
U4: 74LS374; DIP-20_W7.62mm
U5: ATF22V10C; DIP-24_W7.62mm

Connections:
+5V: C1.1, C2.1, C3.1, C4.1, C5.1, C6.1, J1.2, J2.40 (+5V), R1.2, R2.2, R3.2, R4.2, R5.2, R6.2, R7.2, R8.2, R9.1, R16.2, R17.2, SW61.2, SW62.2, U1.14 (VCC), U2.14 (VCC), U3.20 (VCC), U4.20 (VCC), U5.24 (VCC)
A0: J2.26 (A0), U1.9, U2.5
A1: J2.28 (A1), U1.1, U2.9
A2: J2.39 (A2), U1.11, U2.11
A3: J2.33 (A3), U2.1, U5.14
A4: J2.32 (A4), U1.5, U5.15
A5: J2.36 (A5), U1.3, U5.16
A6: J2.37 (A6), U1.13, U5.17
A7: J2.35 (A7), U2.3, U5.20
A8: J2.12 (A8), U5.4
A9: J2.18 (A9), U5.5
A10: J2.3 (A10), U5.6
A11: J2.10 (A11), U5.7
A12: J2.6 (A12), U5.8
A13: J2.5 (A13), U5.9
A14: J2.9 (A14), U5.10
A15: J2.8 (A15), U5.11
D0: J2.29 (D0), U3.3 (O3b), U4.3 (D0)
D1: J2.21 (D1), U3.5 (O2b), U4.4 (D1)
D2: J2.31 (D2), U3.7 (O1b), U4.7 (D2)
D3: J2.25 (D3), U3.9 (O0b), U4.8 (D3)
D4: J2.17 (D4), U3.12 (O3a), U4.13 (D4)
D5: J2.27 (D5), U3.14 (O2a), U4.14 (D5)
D6: J2.23 (D6), U3.16 (O1a), U4.17 (D6)
D7: J2.19 (D7), U3.18 (O0a), U4.18 (D7)
GND: C1.2, C2.2, C3.2, C4.2, C5.2, C6.2, D1.1 (K), D2.1 (K), D3.1 (K), D4.1 (K), D5.1 (K), D6.1 (K), D7.1 (K), J1.4, J2.7 (GND), J2.30 (GND), J2.38 (GND), U1.7 (GND), U2.7 (GND), U3.10 (GND), U4.1 (OE), U4.10 (GND), U5.12 (GND)
unnamed: D1.2 (A), R9.2
unnamed: D2.2 (A), R10.2
unnamed: D3.2 (A), R11.2
unnamed: D4.2 (A), R12.2
unnamed: D5.2 (A), R13.2
unnamed: D6.2 (A), R14.2
unnamed: D7.2 (A), R15.2
unnamed: J1.1, SW62.1
unnamed: J1.3, SW61.1
unnamed: J3.1, R1.1, SW1.2, SW9.2, SW17.2, SW25.2, SW33.2, SW41.2, SW49.2, SW57.2, U3.17 (I3b)
unnamed: J3.2, SW58.2
unnamed: J3.3, R2.1, SW2.2, SW10.2, SW18.2, SW26.2, SW34.2, SW42.2, SW50.2, U3.15 (I2b)
unnamed: R3.1, SW3.2, SW11.2, SW19.2, SW27.2, SW35.2, SW43.2, SW51.2, U3.13 (I1b)
unnamed: R4.1, SW4.2, SW12.2, SW20.2, SW28.2, SW36.2, SW44.2, SW52.2, U3.11 (I0b)
unnamed: R5.1, SW5.2, SW13.2, SW21.2, SW29.2, SW37.2, SW45.2, SW53.2, SW59.2, U3.8 (I3a)
unnamed: R6.1, SW6.2, SW14.2, SW22.2, SW30.2, SW38.2, SW46.2, SW54.2, U3.6 (I2a)
unnamed: R7.1, SW7.2, SW15.2, SW23.2, SW31.2, SW39.2, SW47.2, SW55.2, U3.4 (I1a)
unnamed: R8.1, SW8.2, SW16.2, SW24.2, SW32.2, SW40.2, SW48.2, SW56.2, SW60.2, U3.2 (I0a)
unnamed: R10.1, U4.2 (O0)
unnamed: R11.1, U4.5 (O1)
unnamed: R12.1, U4.6 (O2)
unnamed: R13.1, U4.9 (O3)
unnamed: R14.1, U4.12 (O4)
unnamed: R15.1, U4.15 (O5)
unnamed: R17.1, U2.6, U2.8, U2.10, U5.13
unnamed: SW1.1, SW2.1, SW3.1, SW4.1, SW5.1, SW6.1, SW7.1, SW8.1, U1.8
unnamed: SW9.1, SW10.1, SW11.1, SW12.1, SW13.1, SW14.1, SW15.1, SW16.1, U1.2
unnamed: SW17.1, SW18.1, SW19.1, SW20.1, SW21.1, SW22.1, SW23.1, SW24.1, U1.10
unnamed: SW25.1, SW26.1, SW27.1, SW28.1, SW29.1, SW30.1, SW31.1, SW32.1, U2.2
unnamed: SW33.1, SW34.1, SW35.1, SW36.1, SW37.1, SW38.1, SW39.1, SW40.1, U1.6
unnamed: SW41.1, SW42.1, SW43.1, SW44.1, SW45.1, SW46.1, SW47.1, SW48.1, U1.4
unnamed: SW49.1, SW50.1, SW51.1, SW52.1, SW53.1, SW54.1, SW55.1, SW56.1, U1.12
unnamed: SW57.1, SW58.1, SW59.1, SW60.1, U2.4
unnamed: U2.13, U5.19
unnamed: U3.1 (OEa), U3.19 (OEb), U5.18
unnamed: U4.11 (Cp), U5.23
unnamed: U4.16 (O6), U5.22
unnamed: U4.19 (O7), U5.21
~EXMEM~: J2.4 (~EXMEM~), U5.1
~INUSE~: J2.15 (~INUSE~), R16.1, U2.12
~OUT~: J2.11 (~OUT~), U5.3
~READ~: J2.16 (~RD~), U5.2

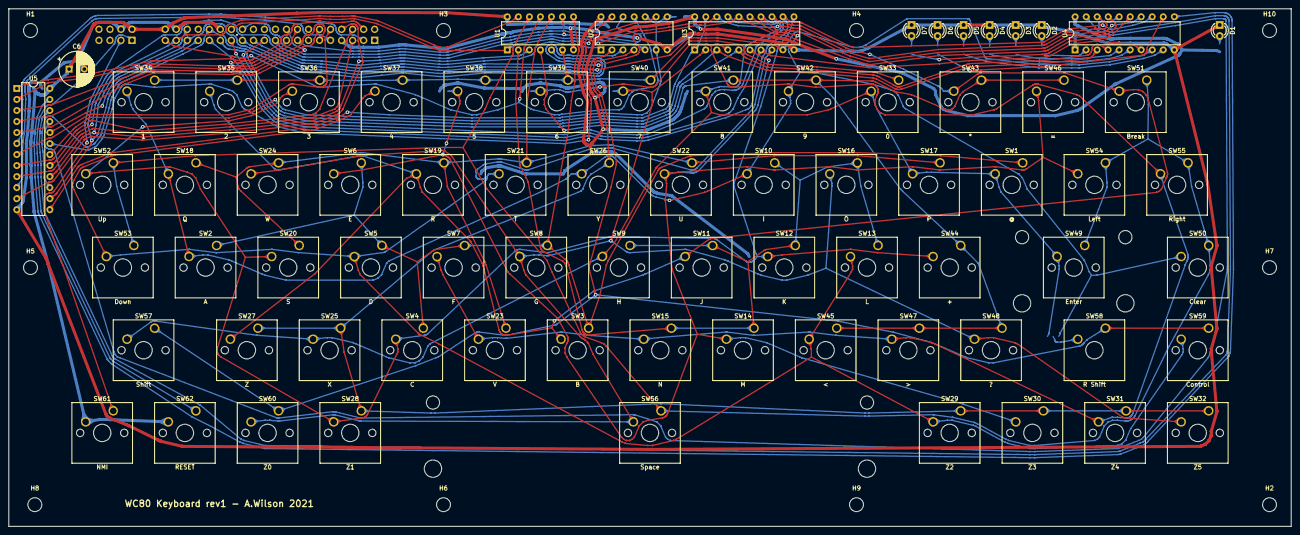
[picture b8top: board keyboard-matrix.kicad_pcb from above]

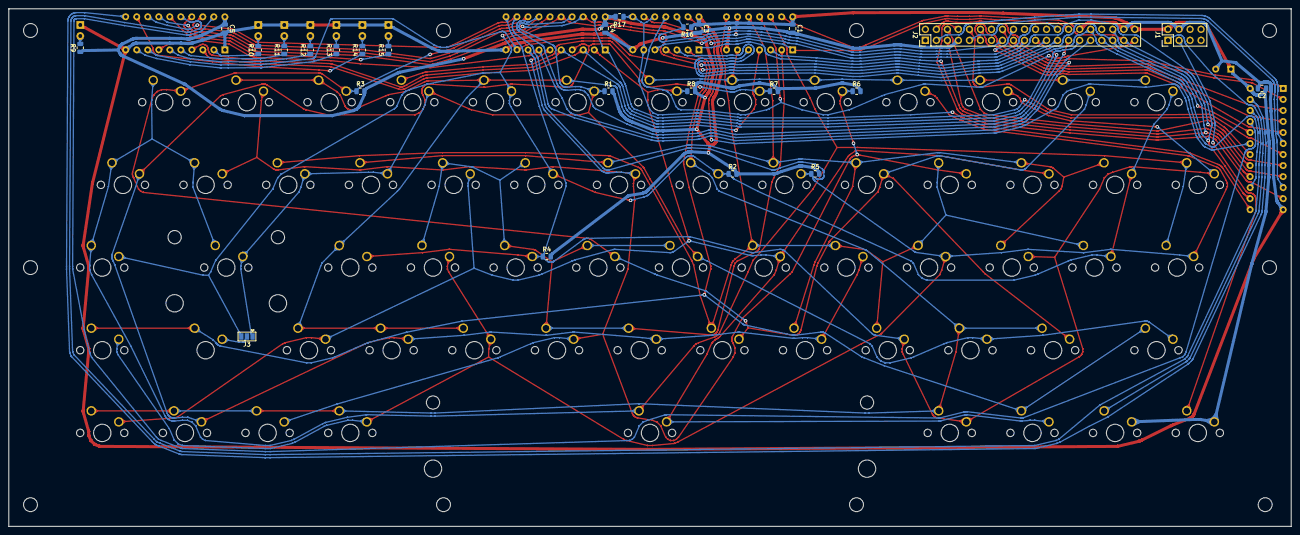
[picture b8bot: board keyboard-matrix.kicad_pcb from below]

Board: 2 copper layers, 295.5 x 119.2 mm, 110 parts (25 on the bottom side), 68 nets.

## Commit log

2025-07-11 first
2025-07-11 bulk file add
2025-07-11 test
2025-07-17 add images, readme
2025-07-17 cpu boards
2025-07-17 keyboard info
